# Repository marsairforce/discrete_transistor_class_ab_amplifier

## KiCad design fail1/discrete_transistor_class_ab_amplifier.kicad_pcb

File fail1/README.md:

# A first attempt at discrete transistor amplifier

This did not work for me at all.

I could not get the output to be biased so the idle voltage was 0 volts.

The input differential stage did not seem to work well for me.

I think there is something about needing to balance transistors, use the correct values of resistances for the transistors I have. But also not knowing how to calculate what those are at this time.

Tried building the circuuit in pieces, just the output, just the input side. Then both together. The feedback is important, and here the feedback takes away most of the actual gain.  But still everything kept getting all hot and I burnt up the output transistors.

I learned a bit about the compound pair transistor configuration. ANd that the differential input needs a constant current source. But then also this schematic looks nothing like other examples I keep seeing.

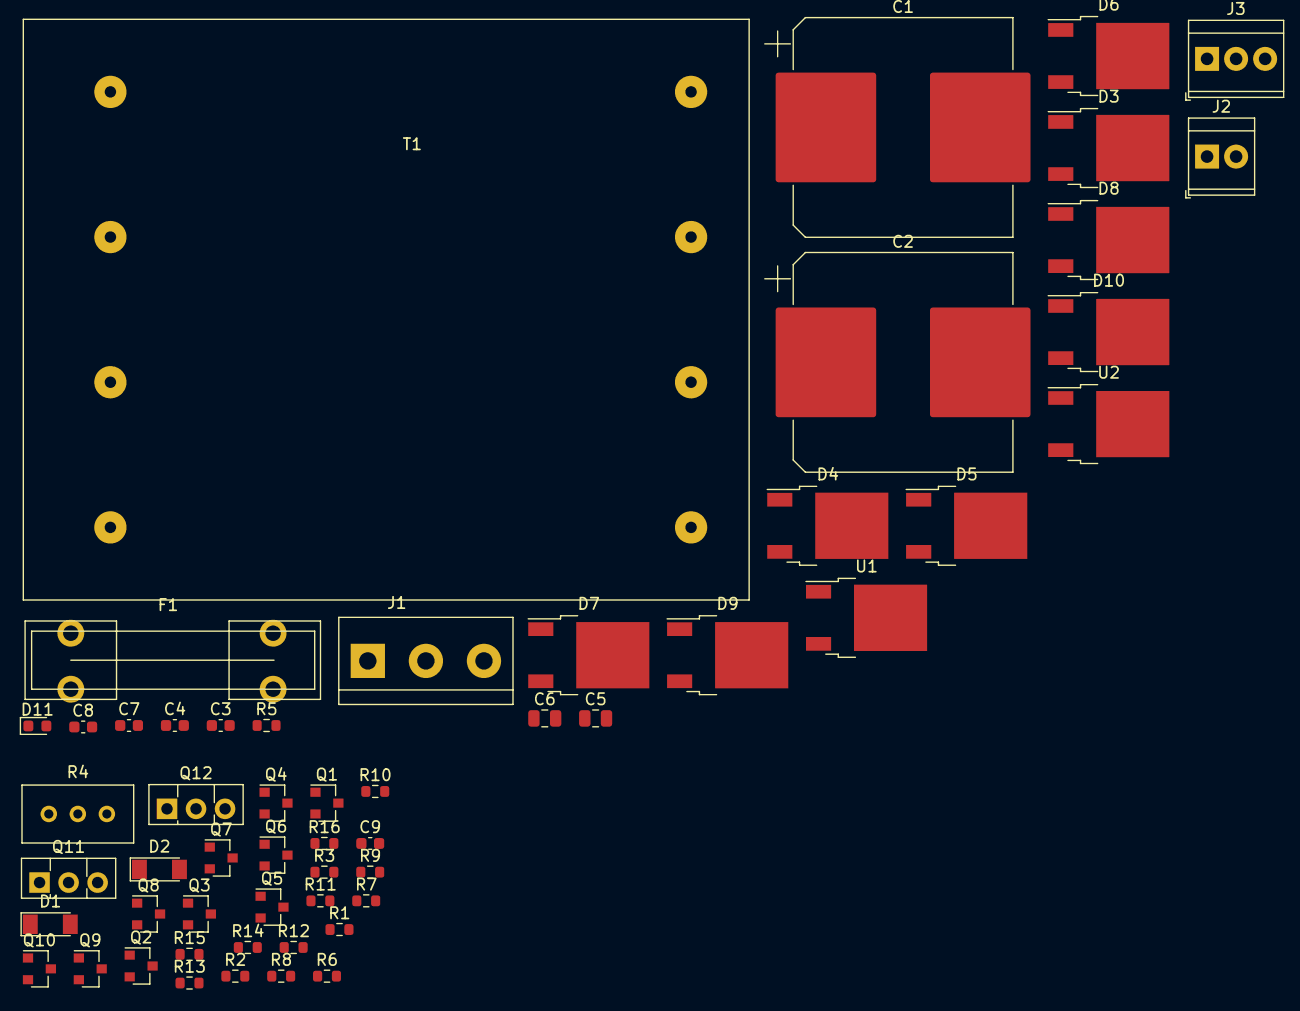
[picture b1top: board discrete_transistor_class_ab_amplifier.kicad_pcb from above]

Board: 2 copper layers, 55 parts (0 on the bottom side), 31 nets, no tracks yet.

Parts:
C1, C2: 3000uF; CP_Elec_18x22
C3, C4, C7, C8: 0.1uF; C_0603_1608Metric
C5, C6: 10uF; C_0805_2012Metric
C9: 250pF; C_0603_1608Metric
D1, D2: LL4148; D_MiniMELF
D3, D4, D5, D6, D7, D8, D9, D10: MBRD6100CTTR; TO-252-2
D11: LED; D_0603_1608Metric
F1: 1A; Fuseholder5x20_horiz_open_lateral_Type-II
J1: AC IN; TerminalBlock-3_P5.08mm
J2: power led; TerminalBlock_1x02_P2.54mm_Horizontal
J3: Power; TerminalBlock_1x03_P2.54mm_Horizontal
Q1, Q3, Q5, Q6, Q7, Q10: MMBT3906; SOT-23
Q2, Q4, Q8, Q9: MMBT3904; SOT-23
Q11: BD140; TO-126-3_Vertical
Q12: BD139; TO-126-3_Vertical
R1, R2, R6, R7: 100; R_0603_1608Metric
R3, R8, R9: 1.8K; R_0603_1608Metric
R4: R_Trim; Potentiometer_Bourns_3296W_Vertical
R5: 10K; R_0603_1608Metric
R10, R11: 68; R_0603_1608Metric
R12: 20K; R_0603_1608Metric
R13, R14: 4.7K; R_0603_1608Metric
R15, R16: 270; R_0603_1608Metric
T1: Hammond_229B34; Transformer_Hammond_229B34
U1: L7815; TO-252-2
U2: L7915; TO-252-2

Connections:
+V: C5.1, C7.1, J3.1, Q6.2, Q11.1, R3.1, R10.1, R13.1, R15.1, U1.3
-V: C6.2, C8.2, J3.3, Q12.1, R2.2, R7.2, R9.2, R11.2, R14.2, R16.2, U2.3
/power_stage/OUT: Q9.2, Q10.2, Q11.2, Q12.2, R12.1
Earth: C1.2, C2.1, C3.2, C4.1, C5.2, C6.1, C7.2, C8.1, D3.1, D3.3, D4.1, D4.3, D9.2, D10.2, J1.2, J3.2, R8.2, U1.2, U2.1
unnamed: C1.1, C3.1, D7.2, D8.2, D11.2, J2.1, U1.1
unnamed: C2.2, C4.2, D5.1, D5.3, D6.1, D6.3, J2.2, R5.2, U2.2
unnamed: C9.1, D2.1, Q7.3, Q8.3, Q10.1, R14.1
unnamed: C9.2, Q1.3, Q2.3, Q8.1
unnamed: D1.1, D2.2
unnamed: D1.2, Q9.1, R13.2
unnamed: D3.2, D7.1, D7.3, T1.7
unnamed: D4.2, D8.1, D8.3, T1.8
unnamed: D5.2, D9.1, D9.3, T1.6
unnamed: D6.2, D10.1, D10.3, T1.5
unnamed: D11.1, R5.1
unnamed: F1.1, T1.1, T1.3
unnamed: F1.2, J1.1
unnamed: J1.3, T1.2, T1.4
unnamed: Q1.2, R1.2
unnamed: Q2.1, Q4.1, Q4.3, Q5.3
unnamed: Q2.2, R2.1, R4.2
unnamed: Q3.1, Q6.3, Q7.1, R9.1
unnamed: Q3.2, Q6.1, R3.2
unnamed: Q3.3, R1.1, R6.1
unnamed: Q4.2, R4.1, R7.1
unnamed: Q5.1, R8.1, R12.2
unnamed: Q5.2, R6.2
unnamed: Q7.2, R10.2
unnamed: Q8.2, R11.1
unnamed: Q10.3, Q12.3, R16.1
unnamed: Q9.3, Q11.3, R15.2

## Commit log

2021-06-06 import
